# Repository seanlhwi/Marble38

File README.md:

# Marble38
A 40percent keyboard with a knob and an acrylic cut out. The name comes from my hopes on printing this with marble filament!
I started to develop this keyboard after watching Joe Scotto's various custom keyboard videos. I was already interested in keyboards, so it seemed natural to try to create one fully custom. I also really wanted to have a keyboard that is small, has a knob, and a unique design. Some key details encludes a rotary encoder for the knob, an acrylic cutout to show the microcontroller, and a unique case shape that seperates it from the other keyboards. Keeping the keyboard compact was one of my main criterias, and I therefore made a very compact 40 percent layout with an additional layer keeping the other keys that I couldn't fit in the main layer. I unexpectedly had trouble with the firmware, however, since I was unable to use the QMK firmware webpage because of my custom layout and knob (My knob is used for increasing and decreasing the volume).

[Marble38BOM.md](https://github.com/user-attachments/files/29319118/Marble38BOM.md)
## Bill of Materials

| Name | Purpose | Qty | Total (USD) | Distributor |
|------|---------|:---:|------------:|-------------|
| [PCB](https://cart.jlcpcb.com/shopcart/cart) | PCB | 5 | $23.00 | JLCPCB |
| [Acrylic Sheet](https://www.aliexpress.us/item/3256804556291038.html?spm=a2g0o.detail.0.0.304fw2L0w2L0v0&mp=1&pdp_npi=6%40dis%21USD%21USD+7.06%21USD+6.90%21%21USD+6.90%21%21%21%402103212317823529591156156ea06e%2112000030310589080%21ct%21US%217547000002%21%211%210%21&gatewayAdapt=glo2usa) | Acrylic Cover | 1 | $6.90 | AliExpress |
| [M2 Screws](https://www.aliexpress.us/item/3256804341271555.html?spm=a2g0o.detail.0.0.11c3fgvnfgvnbD&mp=1&pdp_npi=6%40dis%21USD%21USD+1.13%21USD+1.11%21%21USD+1.11%21%21%21%402103212317823526741237199ea06e%2112000029486656873%21ct%21US%217547000002%21%211%210%21&gatewayAdapt=glo2usa) | Screws | 1 | $1.11 | AliExpress |
| [Keycaps](https://www.amazon.com/gp/product/B0CZLGYJ48/ref=ewc_pr_img_1?smid=A2ASRUM4X82REY&th=1) | Keycaps | 1 | $8.84 | Amazon |
| [Stabilizer](https://www.aliexpress.us/item/3256806342416791.html?spm=a2g0o.productlist.0.0.112352680K8Aiv&mp=1&pdp_npi=6%40dis%21USD%21USD+8.16%21USD+7.46%21%21USD+7.46%21%21%21%402103212317823524874202004ea06e%2112000037543723490%21ct%21US%217547000002%21%211%210%21&gatewayAdapt=glo2usa) | Stabilizing Keys | 1 | $7.46 | AliExpress |
| [SOD-123](https://www.aliexpress.us/item/3256810466885186.html?spm=a2g0o.detail.0.0.66b9beSObeSODp&mp=1&pdp_npi=6%40dis%21USD%21USD+3.86%21USD+1.93%21%21USD+1.93%21%21%21%402103212317823529723976433ea06e%2112000053087454998%21ct%21US%217547000002%21%211%210%21&gatewayAdapt=glo2usa) | Diodes | 1 | $1.93 | AliExpress |
| [Foam Gasket](https://www.aliexpress.us/item/3256805377257558.html?spm=a2g0o.detail.0.0.6aa8avmLavmLxS&mp=1&pdp_npi=6%40dis%21USD%21USD+5.81%21USD+5.81%21%21USD+5.81%21%21%21%402103212317823527347438243ea06e%2112000035901359320%21ct%21US%217547000002%21%211%210%21&gatewayAdapt=glo2usa) | Gasket Mount | 1 | $5.81 | AliExpress |
| [EC11 Rotary Encoder](https://www.aliexpress.us/item/3256807905633617.html?spm=a2g0o.productlist.main.1.cc63gAWPgAWPk3&algo_pvid=cbd3de2e-7ac3-4bae-a663-01251d6630d9&algo_exp_id=cbd3de2e-7ac3-4bae-a663-01251d6630d9-0&pdp_ext_f=%7B%22order%22%3A%22551%22%2C%22eval%22%3A%221%22%2C%22fromPage%22%3A%22search%22%7D&pdp_npi=6%40dis%21USD%213.35%210.99%21%21%213.35%210.99%21%4021030a4b17760592452258933ed8db%2112000043680120684%21sea%21US%217547000002%21ABX%211%210%21n_tag%3A-29910%3Bd%3Ab8015793%3Bm03_new_user%3A-29895%3BpisId%3A5000000203537387&curPageLogUid=WXUKcUE6ifw6&utparam-url=scene%3Asearch%7Cquery_from%3A%7Cx_object_id%3A1005008091948369%7C_p_origin_prod%3A) | Knob | 3 | $2.65 | AliExpress |
| [Tenstar RP2040 Zero](https://www.aliexpress.com/ssr/300000512/BundleDeals2?spm=a2g0o.productlist.main.2.4ee76ed1ZBjVWc&productIds=1005007170764646%3A12000039691235237&pha_manifest=ssr&_immersiveMode=true&disableNav=YES&sourceName=SEARCHProduct&utparam-url=scene%3Asearch%7Cquery_from%3A%7Cx_object_id%3A1005007170764646%7C_p_origin_prod%3A1005005618101831&pvid=24b1b4a4-ad2e-4def-b067-1604bb128a50) | Microcontroller | 2 | $2.26 | AliExpress |
| [Soldering Wire](https://www.aliexpress.com/ssr/300000512/BundleDeals2?spm=a2g0o.productlist.main.2.4ee76ed1ZBjVWc&productIds=1005007170764646%3A12000039691235237&pha_manifest=ssr&_immersiveMode=true&disableNav=YES&sourceName=SEARCHProduct&utparam-url=scene%3Asearch%7Cquery_from%3A%7Cx_object_id%3A1005007170764646%7C_p_origin_prod%3A1005005618101831&pvid=24b1b4a4-ad2e-4def-b067-1604bb128a50) | Soldering | 1 | $1.13 | AliExpress |
| **Total** | | | **$61.09** | |

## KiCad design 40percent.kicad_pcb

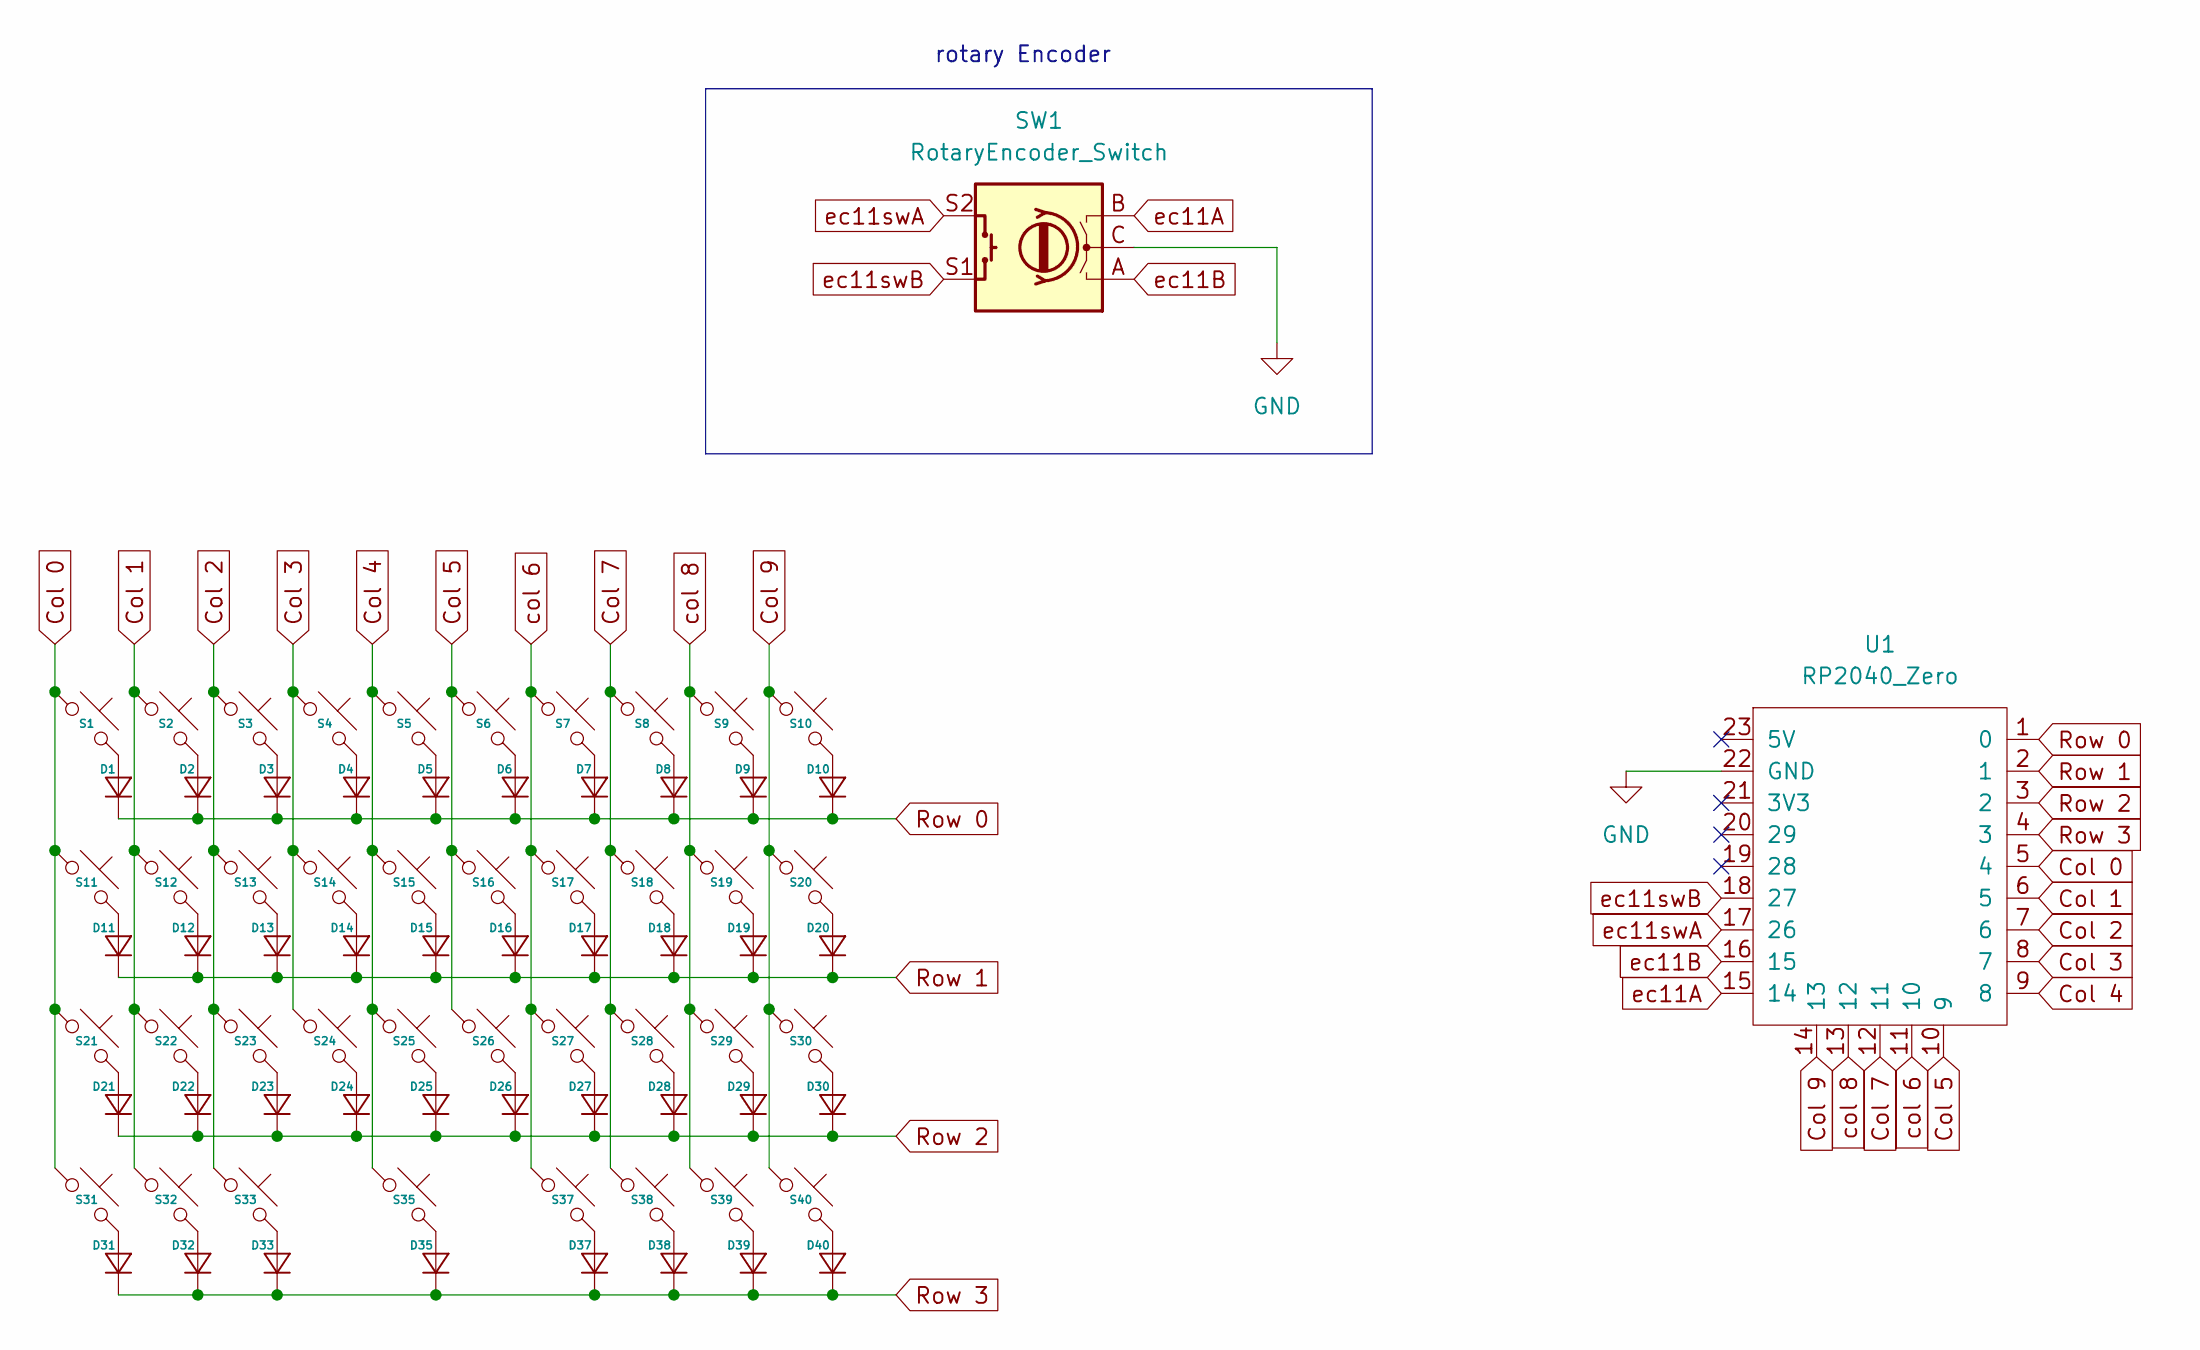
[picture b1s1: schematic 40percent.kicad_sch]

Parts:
D1, D2, D3, D4, D5, D6, D7, D8, D9, D10, D11, D12, D13, D14, D15, D16, D17, D18, D19, D20, D21, D22, D23, D24, D25, D26, D27, D28, D29, D30, D31, D32, D33, D35, D37, D38, D39, D40: Diode_SOD-123
S1, S2, S3, S4, S5, S6, S7, S8, S9, S10, S11, S12, S13, S14, S15, S16, S17, S18, S19, S20, S21, S22, S23, S24, S25, S26, S27, S28, S29, S30, S31, S32, S33, S35, S37, S38, S39, S40: MX_PCB_1.00u
SW1: RotaryEncoder_Switch; RotaryEncoder_Alps_EC11E-Switch_Vertical_H20mm
U1: RP2040_Zero

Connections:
Col 0: S1.1, S11.1, S21.1, S31.1, U1.5 (4)
Col 1: S2.1, S12.1, S22.1, S32.1, U1.6 (5)
Col 2: S3.1, S13.1, S23.1, S33.1, U1.7 (6)
Col 3: S4.1, S14.1, S24.1, U1.8 (7)
Col 4: S5.1, S15.1, S25.1, S35.1, U1.9 (8)
Col 5: S6.1, S16.1, S26.1, U1.10 (9)
Col 7: S8.1, S18.1, S28.1, S38.1, U1.12 (11)
Col 9: S10.1, S20.1, S30.1, S40.1, U1.14 (13)
GND: SW1.C, U1.22 (GND)
unnamed: D1.2 (A), S1.2
unnamed: D2.2 (A), S2.2
unnamed: D3.2 (A), S3.2
unnamed: D4.2 (A), S4.2
unnamed: D5.2 (A), S5.2
unnamed: D6.2 (A), S6.2
unnamed: D7.2 (A), S7.2
unnamed: D8.2 (A), S8.2
unnamed: D9.2 (A), S9.2
unnamed: D10.2 (A), S10.2
unnamed: D11.2 (A), S11.2
unnamed: D12.2 (A), S12.2
unnamed: D13.2 (A), S13.2
unnamed: D14.2 (A), S14.2
unnamed: D15.2 (A), S15.2
unnamed: D16.2 (A), S16.2
unnamed: D17.2 (A), S17.2
unnamed: D18.2 (A), S18.2
unnamed: D19.2 (A), S19.2
unnamed: D20.2 (A), S20.2
unnamed: D21.2 (A), S21.2
unnamed: D22.2 (A), S22.2
unnamed: D23.2 (A), S23.2
unnamed: D24.2 (A), S24.2
unnamed: D25.2 (A), S25.2
unnamed: D26.2 (A), S26.2
unnamed: D27.2 (A), S27.2
unnamed: D28.2 (A), S28.2
unnamed: D29.2 (A), S29.2
unnamed: D30.2 (A), S30.2
unnamed: D31.2 (A), S31.2
unnamed: D32.2 (A), S32.2
unnamed: D33.2 (A), S33.2
unnamed: D35.2 (A), S35.2
unnamed: D37.2 (A), S37.2
unnamed: D38.2 (A), S38.2
unnamed: D39.2 (A), S39.2
unnamed: D40.2 (A), S40.2
Row 0: D1.1 (K), D2.1 (K), D3.1 (K), D4.1 (K), D5.1 (K), D6.1 (K), D7.1 (K), D8.1 (K), D9.1 (K), D10.1 (K), U1.1 (0)
Row 1: D11.1 (K), D12.1 (K), D13.1 (K), D14.1 (K), D15.1 (K), D16.1 (K), D17.1 (K), D18.1 (K), D19.1 (K), D20.1 (K), U1.2 (1)
Row 2: D21.1 (K), D22.1 (K), D23.1 (K), D24.1 (K), D25.1 (K), D26.1 (K), D27.1 (K), D28.1 (K), D29.1 (K), D30.1 (K), U1.3 (2)
Row 3: D31.1 (K), D32.1 (K), D33.1 (K), D35.1 (K), D37.1 (K), D38.1 (K), D39.1 (K), D40.1 (K), U1.4 (3)
col 6: S7.1, S17.1, S27.1, S37.1, U1.11 (10)
col 8: S9.1, S19.1, S29.1, S39.1, U1.13 (12)
ec11A: SW1.B, U1.15 (14)
ec11B: SW1.A, U1.16 (15)
ec11swA: SW1.S2, U1.17 (26)
ec11swB: SW1.S1, U1.18 (27)

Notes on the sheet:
rotary Encoder

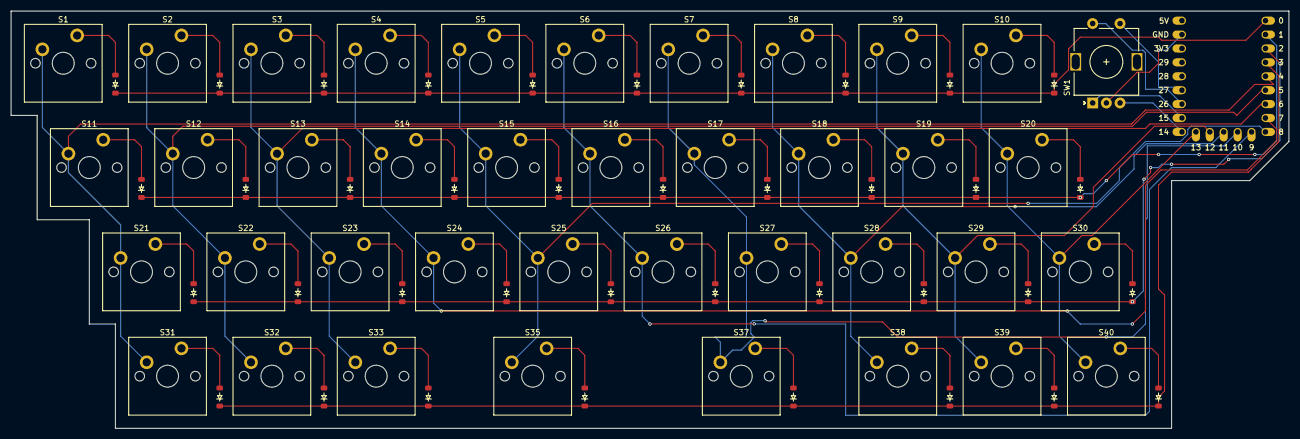
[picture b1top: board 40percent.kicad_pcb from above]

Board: 2 copper layers, 233.4 x 76.2 mm, 78 parts (0 on the bottom side), 57 nets.

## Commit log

2026-03-29 Create CAD
2026-04-22 Add images to README for visual reference
    Added images to enhance the README description.
2026-04-22 Add BOM file with component details
2026-04-22 Create BOM
2026-04-22 Update print statement from 'Hello' to 'Goodbye'
2026-04-23 Create Footprints
2026-04-23 Rename Libraries/Footprints to Libraries/Libraries/Marble38.pretty/Choc_V1V2.kicad_mod
2026-04-23 Reorganize footprints into Libraries folder
2026-04-23 Reorganize files into correct folders
2026-04-23 Rename marble38_default.uf2 to Firmware
2026-04-24 Rename Marble38 - 시트1 (2).csv to BOM
2026-04-25 Create gitkeep
2026-04-27 Rename Marble38 - 시트1 (2).csv to Marble38.csv
2026-05-05 Create Onshape Link
2026-05-06 Revise Bill of Materials format and links
    Updated the Bill of Materials section with new formatting and links.
2026-06-14 Update Marble38
2026-06-14 Refine README introduction for Marble38 keyboard
    Reworded the introduction for clarity and flow.
2026-06-25 Create Fake
